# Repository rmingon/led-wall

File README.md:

# LED-Wall Tile — CH32V003 Parallel-Bus WS2812B Controller (5×5)

A modular **5×5 WS2812B LED tile** driven by a **CH32V003** slave MCU.  
Tiles share a simple **8-bit parallel bus + CLK + EN** so a Raspberry Pi (or any MCU) can address many tiles and push pixel data quickly.

---

## Highlights

- **25× WS2812B** per tile (5 rows × 5 columns), daisy-chained on-board
- **Parallel control bus:** `DATA0…DATA7`, `CLK`, `EN`, optional `RST`
- **MCU:** WCH **CH32V003F…** (RISC-V, 3.3 V)
- **Power:** 5 V input for LEDs; onboard **AMS1117-3.3** LDO for the MCU
- **Connectors on four edges** for tiling/rotation; pass-through for power & bus
- **Status LED** on a GPIO for quick diagnostics
- Designed with **KiCad 9.0.3**

---

## Repo structure

```
/wall/
  wall.kicad_pro
  wall.kicad_pcb
  wall.kicad_sch
  wall.kicad_prl
/media/
  wall_top_3d.jpeg
  wall_bottom_3d.jpeg
  wall_pcb.png
  wall_schematic.png
/firmware/        # (placeholder) CH32V003 code
/tools/           # (placeholder) host examples (Raspberry Pi)
README.md
```

---

## Images

- Top 3D: `media/wall_top_3d.jpeg`
- Bottom 3D: `media/wall_bottom_3d.jpeg`
- PCB layout: `media/wall_pcb.png`
- Schematic: `media/wall_schematic.png`

---

## Electrical overview

- **LED matrix:** 25 × WS2812B (5050). Data is routed serpentine per row.
- **MCU:** `CH32V003F*P6` (labelled **U1** in the schematic).
  - Parallel data bus on **PC0…PC7**
  - `CLK` and `EN` on PDx pins (see net labels in schematic)
  - `PA1/PA2` used for the **WS2812** data output to the first LED in the chain
  - `RST` net broken out (optional external reset)
- **Power:**
  - **+5 V** for LEDs
  - **AMS1117-3.3** (U3) generates **+3V3** for the MCU; C1/C2/C3 for decoupling
- **Indicators:** D26 + R4 connected to a GPIO (status / heartbeat)

> ⚠️ **Current budget:** Each WS2812B can draw up to **40 mA** at full-white.  
> One tile worst-case ≈ **25 × 40 mA = 1.5 A @ 5 V** (plus margin).  
> Size your power rails accordingly and avoid sustained full-white if thermals are tight.

---

## Connectors / Pinout

Each edge header is a **1×14** connector carrying power and the parallel bus.

| Pin | Signal | Notes                              |
| --: | :----- | :--------------------------------- |
|   1 | DATA0  | Parallel data bit 0 (MCU **PC0**)  |
|   2 | DATA1  | (PC1)                              |
|   3 | DATA2  | (PC2)                              |
|   4 | DATA3  | (PC3)                              |
|   5 | DATA4  | (PC4)                              |
|   6 | DATA5  | (PC5)                              |
|   7 | DATA6  | (PC6)                              |
|   8 | DATA7  | (PC7)                              |
|   9 | CLK    | Rising edge latch (EXTI7_0 IRQ)    |
|  10 | EN     | Tile enable / latch (PDx)          |
|  11 | GND    | Ground                             |
|  12 | GND    | Ground (second pin for current)    |
|  13 | +5V    | LED power                          |
|  14 | +5V    | LED power (second pin for current) |

> Exact PDx assignments are labelled in the schematic nets; keep those in firmware defines so you can move them if the footprint changes.

- WS2812 data → **PC7 / TIM2_CH2 (remap)**
- Driven by **TIM2 PWM + DMA**

---

## Protocol

Each frame is transmitted as a sequence of **bytes** clocked on **PD2 rising edge** while the slave samples D0–D7.

**Frame format:**

```
SOF0 SOF1 ADDR CMD LEN PAY[LEN] CRC
```

- **SOF0** = `0xA5`
- **SOF1** = `0x5A`
- **ADDR** = 0–254 for unicast, `0xFF` for broadcast
- **CMD** = command byte
- **LEN** = number of payload bytes
- **PAY** = payload
- **CRC** = Dallas/Maxim CRC8 (poly=0x31 reflected=0x8C, init=0x00) computed over `ADDR..CMD..LEN..PAY`

### Commands

| CMD  | Name          | LEN      | Payload description             |
| ---- | ------------- | -------- | ------------------------------- |
| 0x01 | `SET_ALL_RGB` | 3×N (75) | [R,G,B] triplets for all LEDs   |
| 0x02 | `SET_ONE_RGB` | 4        | [index, R, G, B] (0–24 index)   |
| 0x03 | `FILL_RGB`    | 3        | [R, G, B] fill all LEDs         |
| 0x04 | `BOOT_TEST`   | 0        | Run built-in RGB test animation |

---

## Firmware (CH32V003)

- **Toolchain:** WCH-RISC-V (MounRiver) or Open-source (e.g., `riscv-none-elf-gcc` + `openocd` for WCH-LinkE).
- **Peripherals used:**
  - GPIO for `DATA[7:0]`, `CLK`, `EN`, `LED`
  - Timer or edge-detect to sample `CLK` while `EN=1`
  - Bit-banged or timer-driven WS2812 waveform output on `PAx`
- **WS2812 timing:** 800 kHz, 1.25 µs/bit. Use a timer and tight ISR/DMA-like loop to meet timing.

**Build steps (outline):**

1. Clone repo; open `/kicad/wall.kicad_pro` to view hardware.
2. Open `/wall_code/` in your IDE; set your tile address in `main.c`.
3. Flash with **WCH-LinkE** via **SWIO** (PD1 on CH32V003). Provide a small 3-pin tag-connector or pogo-pads on your programmer.
4. Power at 5 V and verify the heartbeat LED.

---

## Example Host Frame

Set all 25 LEDs to **red (255,0,0)**:

```
A5 5A 12 01 4B  FF 00 00 FF 00 00 ... (25 triplets) ... CRC
```

- `0xA5 0x5A` = SOF
- `0x12` = target address
- `0x01` = `SET_ALL_RGB`
- `0x4B` = 75 payload bytes
- Payload = 25× [FF,00,00]
- `CRC` = computed over ADDR..PAYLOAD

## Raspberry Pi example (Python, pseudo-code)

2. Open `host.py` in your IDE.

## Example Host Frame

Set all 25 LEDs to **red (255,0,0)**:

```
A5 5A 12 01 4B  FF 00 00 FF 00 00 ... (25 triplets) ... CRC
```

- `0xA5 0x5A` = SOF
- `0x12` = target address
- `0x01` = `SET_ALL_RGB`
- `0x4B` = 75 payload bytes
- Payload = 25× [FF,00,00]
- `CRC` = computed over ADDR..PAYLOAD

---

## Manufacturing notes

- **Layers:** 2-layer, 1.6 mm FR-4, 1 oz Cu
- **Min track/clearance:** per your fab defaults (design uses moderate widths)
- **Finish:** HASL or ENIG
- **Decoupling:** place 0.1 µF near the MCU VDD and each LED power rail segment
- **Mounting:** corner holes + through-grid holes in the LED field (for diffusion/weight).

---

## Bring-up checklist

1. Power at **5 V** and check **+3V3** out of U3 (AMS1117-3.3).
2. Flash firmware; confirm status LED blinks.
3. With a logic analyzer, verify `CLK` edges and that `DATA[7:0]` are stable at each edge while `EN=1`.
4. Send a **Fill** command to a single address → tile lights uniformly.
5. Push a full **75-byte** pixel buffer → verify 5×5 order matches your mapping.

---

## License

- Hardware: CC-BY-SA 4.0
- Firmware/Host code: MIT

---

## Credits

Designed by **RMINGON**.  
KiCad project files: `kicad/wall.*` (created with KiCad **9.0.3**).

---

### Bill-of-Materials (core)

| Ref     | Part                  | Notes                                              |
| ------- | --------------------- | -------------------------------------------------- |
| U1      | **CH32V003F…P6**      | 3.3 V RISC-V MCU                                   |
| U3      | **AMS1117-3.3**       | 5 V → 3.3 V LDO                                    |
| D1–D25  | **WS2812B**           | 5 V addressable LEDs                               |
| D26, R4 | Status LED + 5 Ω–1 kΩ | (value per brightness; schematic shows **R4 5 Ω**) |
| J1–J4   | 1×14 headers          | Bus + Power                                        |
| C1–C3   | 10 µF/0.1 µF mix      | Regulator & MCU decoupling                         |

> Tweak values to match your inventory and regulator stability requirements (e.g., AMS1117 likes ≥10 µF on input/output).

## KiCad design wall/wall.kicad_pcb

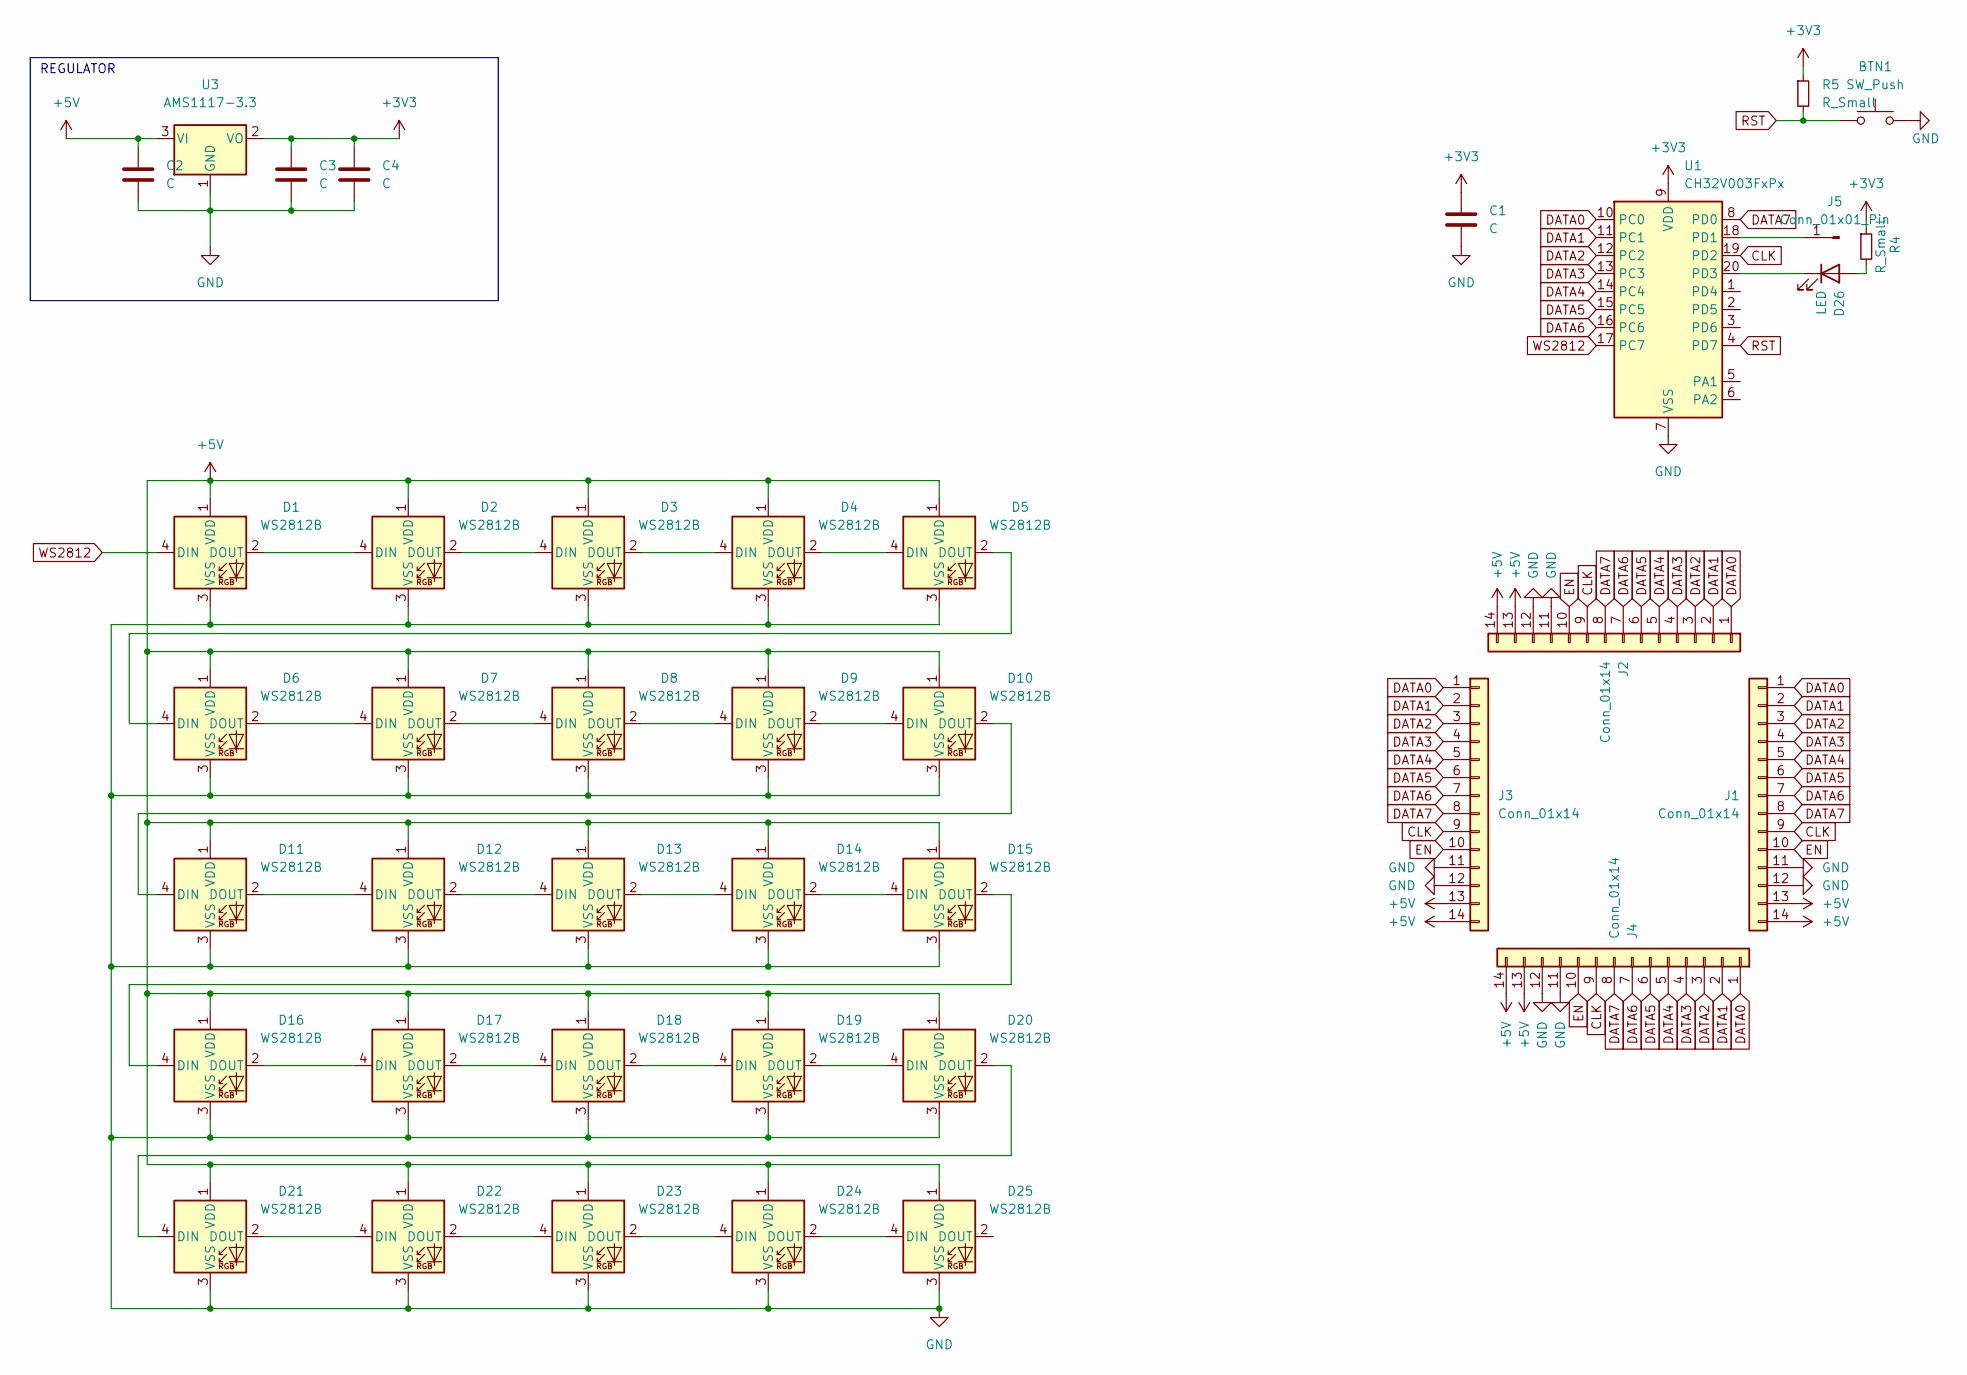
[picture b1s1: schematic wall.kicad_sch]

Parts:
BTN1: SW_Push; SW_SPST_FSMSM; LCSC C398053
C1, C2, C4: C; C_0603_1608Metric; LCSC C30926
C3: C; C_0603_1608Metric; LCSC C19702
D1, D2, D3, D4, D5, D6, D7, D8, D9, D10, D11, D12, D13, D14, D15, D16, D17, D18, D19, D20, D21, D22, D23, D24, D25: WS2812B; LED_WS2812B_PLCC4_5.0x5.0mm_P3.2mm
D26: LED; LED_0603_1608Metric; LCSC C19171301
J1, J2, J3, J4: Conn_01x14; PinSocket_1x14_P2.54mm_Horizontal
J5: Conn_01x01_Pin; TestPoint_Pad_D2.0mm
R4: R_Small; R_0603_1608Metric; LCSC C2906975
R5: R_Small; R_0603_1608Metric; LCSC C98220
U1: CH32V003FxPx; TSSOP-20_4.4x6.5mm_P0.65mm
U3: AMS1117-3.3; SOT-223-3_TabPin2; LCSC C6186

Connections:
+3V3: C1.1, C3.1, C4.1, R4.1, R5.1, U1.9 (VDD), U3.2 (VO)
+5V: C2.1, D1.1 (VDD), D2.1 (VDD), D3.1 (VDD), D4.1 (VDD), D5.1 (VDD), D6.1 (VDD), D7.1 (VDD), D8.1 (VDD), D9.1 (VDD), D10.1 (VDD), D11.1 (VDD), D12.1 (VDD), D13.1 (VDD), D14.1 (VDD), D15.1 (VDD), D16.1 (VDD), D17.1 (VDD), D18.1 (VDD), D19.1 (VDD), D20.1 (VDD), D21.1 (VDD), D22.1 (VDD), D23.1 (VDD), D24.1 (VDD), D25.1 (VDD), J1.13, J1.14, J2.13, J2.14, J3.13, J3.14, J4.13, J4.14, U3.3 (VI)
CLK: J1.9, J2.9, J3.9, J4.9, U1.19 (PD2)
DATA0: J1.1, J2.1, J3.1, J4.1, U1.10 (PC0)
DATA1: J1.2, J2.2, J3.2, J4.2, U1.11 (PC1)
DATA2: J1.3, J2.3, J3.3, J4.3, U1.12 (PC2)
DATA3: J1.4, J2.4, J3.4, J4.4, U1.13 (PC3)
DATA4: J1.5, J2.5, J3.5, J4.5, U1.14 (PC4)
DATA5: J1.6, J2.6, J3.6, J4.6, U1.15 (PC5)
DATA6: J1.7, J2.7, J3.7, J4.7, U1.16 (PC6)
DATA7: J1.8, J2.8, J3.8, J4.8, U1.8 (PD0)
EN: J1.10, J2.10, J3.10, J4.10
GND: BTN1.2, C1.2, C2.2, C3.2, C4.2, D1.3 (VSS), D2.3 (VSS), D3.3 (VSS), D4.3 (VSS), D5.3 (VSS), D6.3 (VSS), D7.3 (VSS), D8.3 (VSS), D9.3 (VSS), D10.3 (VSS), D11.3 (VSS), D12.3 (VSS), D13.3 (VSS), D14.3 (VSS), D15.3 (VSS), D16.3 (VSS), D17.3 (VSS), D18.3 (VSS), D19.3 (VSS), D20.3 (VSS), D21.3 (VSS), D22.3 (VSS), D23.3 (VSS), D24.3 (VSS), D25.3 (VSS), J1.11, J1.12, J2.11, J2.12, J3.11, J3.12, J4.11, J4.12, U1.7 (VSS), U3.1 (GND)
unnamed: D1.2 (DOUT), D2.4 (DIN)
unnamed: D2.2 (DOUT), D3.4 (DIN)
unnamed: D3.2 (DOUT), D4.4 (DIN)
unnamed: D4.2 (DOUT), D5.4 (DIN)
unnamed: D5.2 (DOUT), D6.4 (DIN)
unnamed: D6.2 (DOUT), D7.4 (DIN)
unnamed: D7.2 (DOUT), D8.4 (DIN)
unnamed: D8.2 (DOUT), D9.4 (DIN)
unnamed: D9.2 (DOUT), D10.4 (DIN)
unnamed: D10.2 (DOUT), D11.4 (DIN)
unnamed: D11.2 (DOUT), D12.4 (DIN)
unnamed: D12.2 (DOUT), D13.4 (DIN)
unnamed: D13.2 (DOUT), D14.4 (DIN)
unnamed: D14.2 (DOUT), D15.4 (DIN)
unnamed: D15.2 (DOUT), D16.4 (DIN)
unnamed: D16.2 (DOUT), D17.4 (DIN)
unnamed: D17.2 (DOUT), D18.4 (DIN)
unnamed: D18.2 (DOUT), D19.4 (DIN)
unnamed: D19.2 (DOUT), D20.4 (DIN)
unnamed: D20.2 (DOUT), D21.4 (DIN)
unnamed: D21.2 (DOUT), D22.4 (DIN)
unnamed: D22.2 (DOUT), D23.4 (DIN)
unnamed: D23.2 (DOUT), D24.4 (DIN)
unnamed: D24.2 (DOUT), D25.4 (DIN)
unnamed: D26.2 (A), R4.2
unnamed: D26.1 (K), U1.20 (PD3)
unnamed: J5.1, U1.18 (PD1)
RST: BTN1.1, R5.2, U1.4 (PD7)
WS2812: D1.4 (DIN), U1.17 (PC7)

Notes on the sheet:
REGULATOR

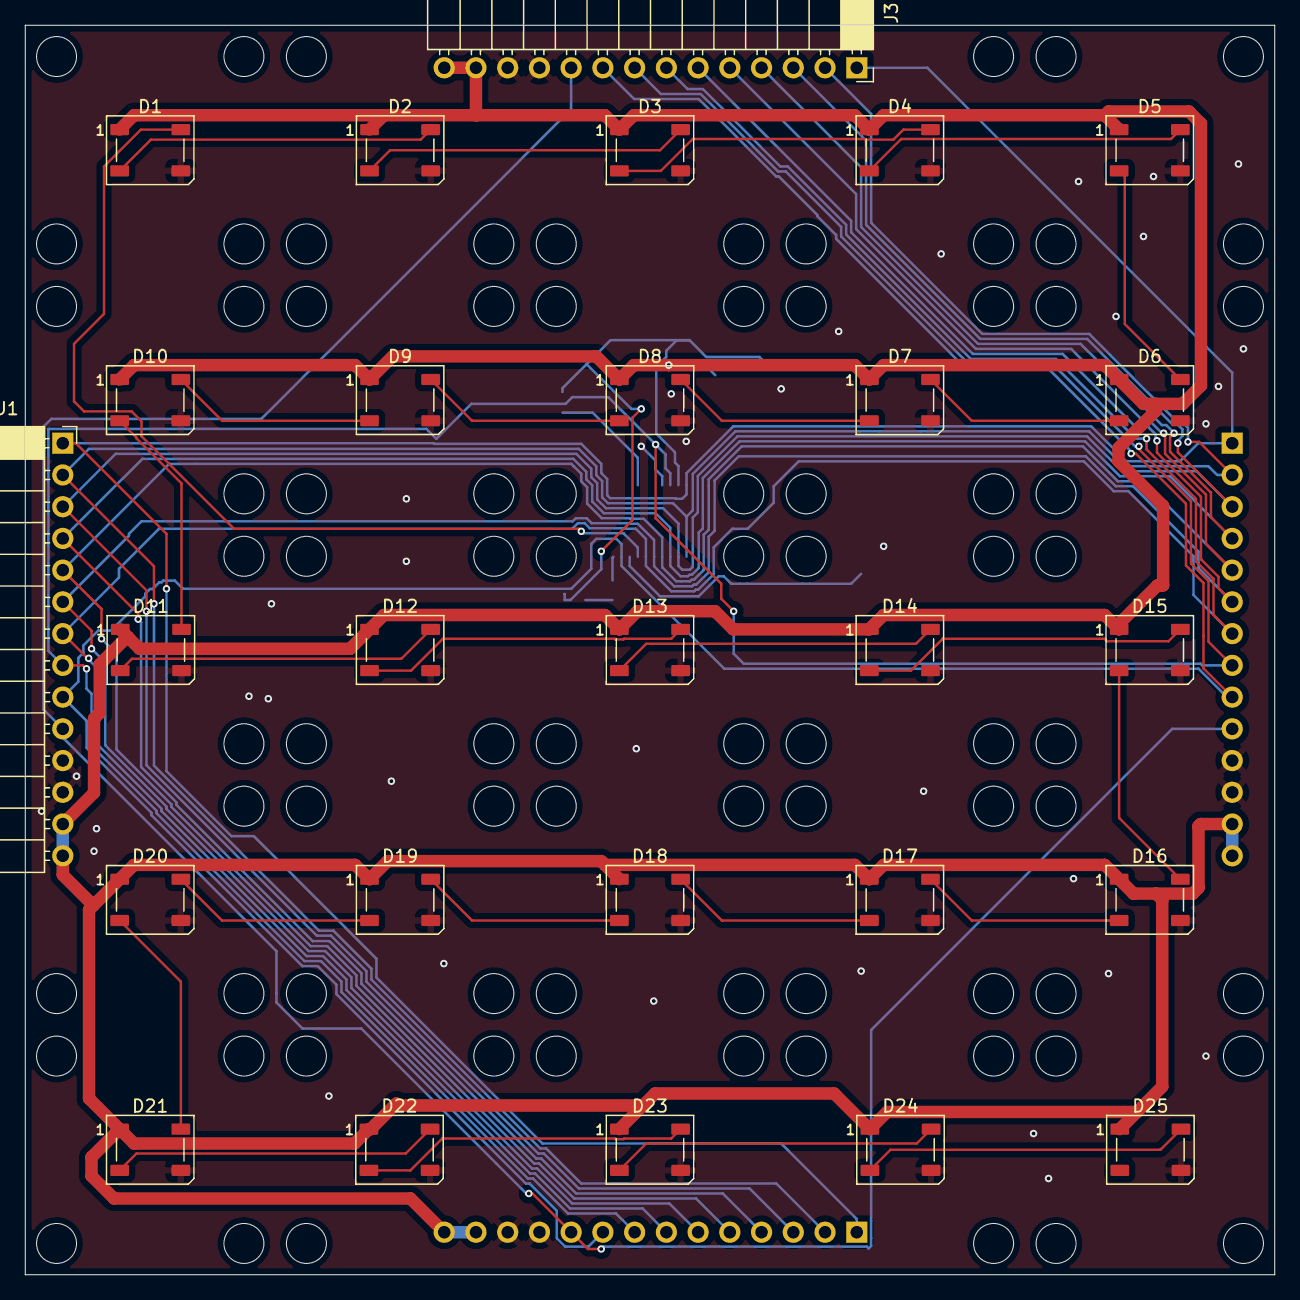
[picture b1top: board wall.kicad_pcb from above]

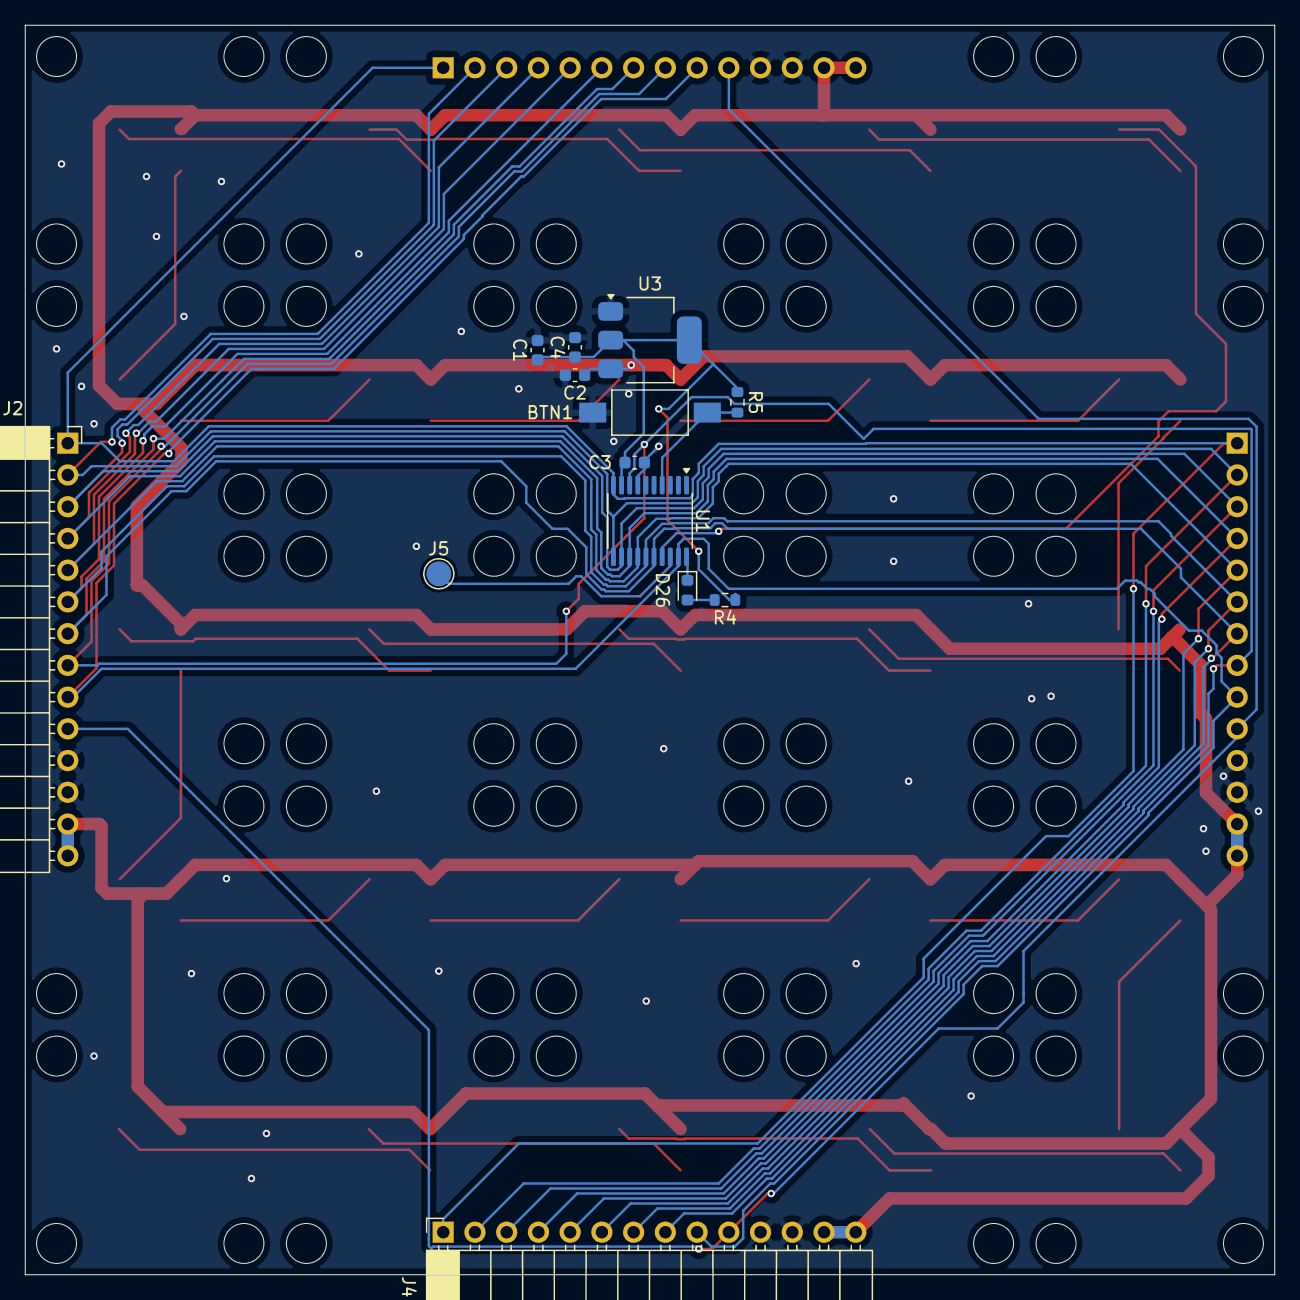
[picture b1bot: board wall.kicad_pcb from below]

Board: 2 copper layers, 100.0 x 100.0 mm, 40 parts (13 on the bottom side), 42 nets.

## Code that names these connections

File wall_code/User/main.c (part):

/* ============================================================
 * CH32V006 SLAVE: WS2812 (PC7, TIM2+DMA) + 8-bit bus + address
 *  Data bus: PC0..PC6 = D0..D6, PD0 = D7
 *  Clock   : PD2 rising edge (EXTI lines 0..7 → EXTI7_0 IRQ)
 *  LEDs    : WS2812 on PC7 via TIM2_CH2 remap + DMA1 Channel2
 * ============================================================ */

#include "debug.h"
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    }
}

/* Remap TIM2_CH2 → PC7; set PC7 AF-PP; configure TIM2 + UDE */
static void WS_LL_Init(void) {
    RCC->PB2PCENR |= (1u<<0) /*AFIOEN*/ | (1u<<4) /*IOPCEN*/;
    RCC->PB1PCENR |= (1u<<0) /*TIM2EN*/;
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
    AFIO->PCFR1 = (AFIO->PCFR1 & ~(0x7u << 14)) | (0x3u << 14);

    /* PC7 = AF push-pull, 30 MHz */
    GPIOC->CFGLR &= ~(0xFu << (7*4));
    GPIOC->CFGLR |=  (0xBu << (7*4)); /* MODE=11, CNF=10 */

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
/* ============================================================
 *                   Parallel bus + framing
 *  Data: PC0..6 = D0..D6, PD0 = D7
 *  Clock: PD2 rising edge → EXTI7_0_IRQHandler
 * ============================================================ */
#define RX_MAX (3*NUM_LEDS + 8)

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    return crc;
}

/* Read D[7:0] : PC0..6→D0..6, PD0→D7 */
static inline uint8_t BUS_ReadByte(void){
    uint32_t c = GPIOC->INDR;
    uint32_t d = GPIOD->INDR;
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    return v;
}

/* Configure inputs + EXTI on PD2 */
static void ParallelBus_Init(void){
    RCC_PB2PeriphClockCmd(RCC_PB2Periph_AFIO | RCC_PB2Periph_GPIOC | RCC_PB2Periph_GPIOD, ENABLE);

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    NVIC_Init(&nv);
}

/* EXTI lines 0..7 ISR (PD2 rising) */
void EXTI7_0_IRQHandler(void){
    if (EXTI_GetITStatus(EXTI_Line2) != RESET){
        uint8_t b = BUS_ReadByte();
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    SystemInit();
    Delay_Init();

    WS_LL_Init();        /* PC7 TIM2+DMA driver ready */
    ParallelBus_Init();  /* PD2 clock, PC0..6+PD0 data */

    WS_BootTest();       /* power-on self-test */

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
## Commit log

2025-07-20 add wall schematic + pcb
2025-09-04 fix wall pcb
2025-09-04 create code for ch32v006 ws2812 control
2025-09-04 add pictures
2025-09-04 add minimal code for control via bus
2025-09-04 upgrade for control via bus CRC
2025-09-04 add host code example
2025-09-04 add readme
2025-09-04 add gitignore
